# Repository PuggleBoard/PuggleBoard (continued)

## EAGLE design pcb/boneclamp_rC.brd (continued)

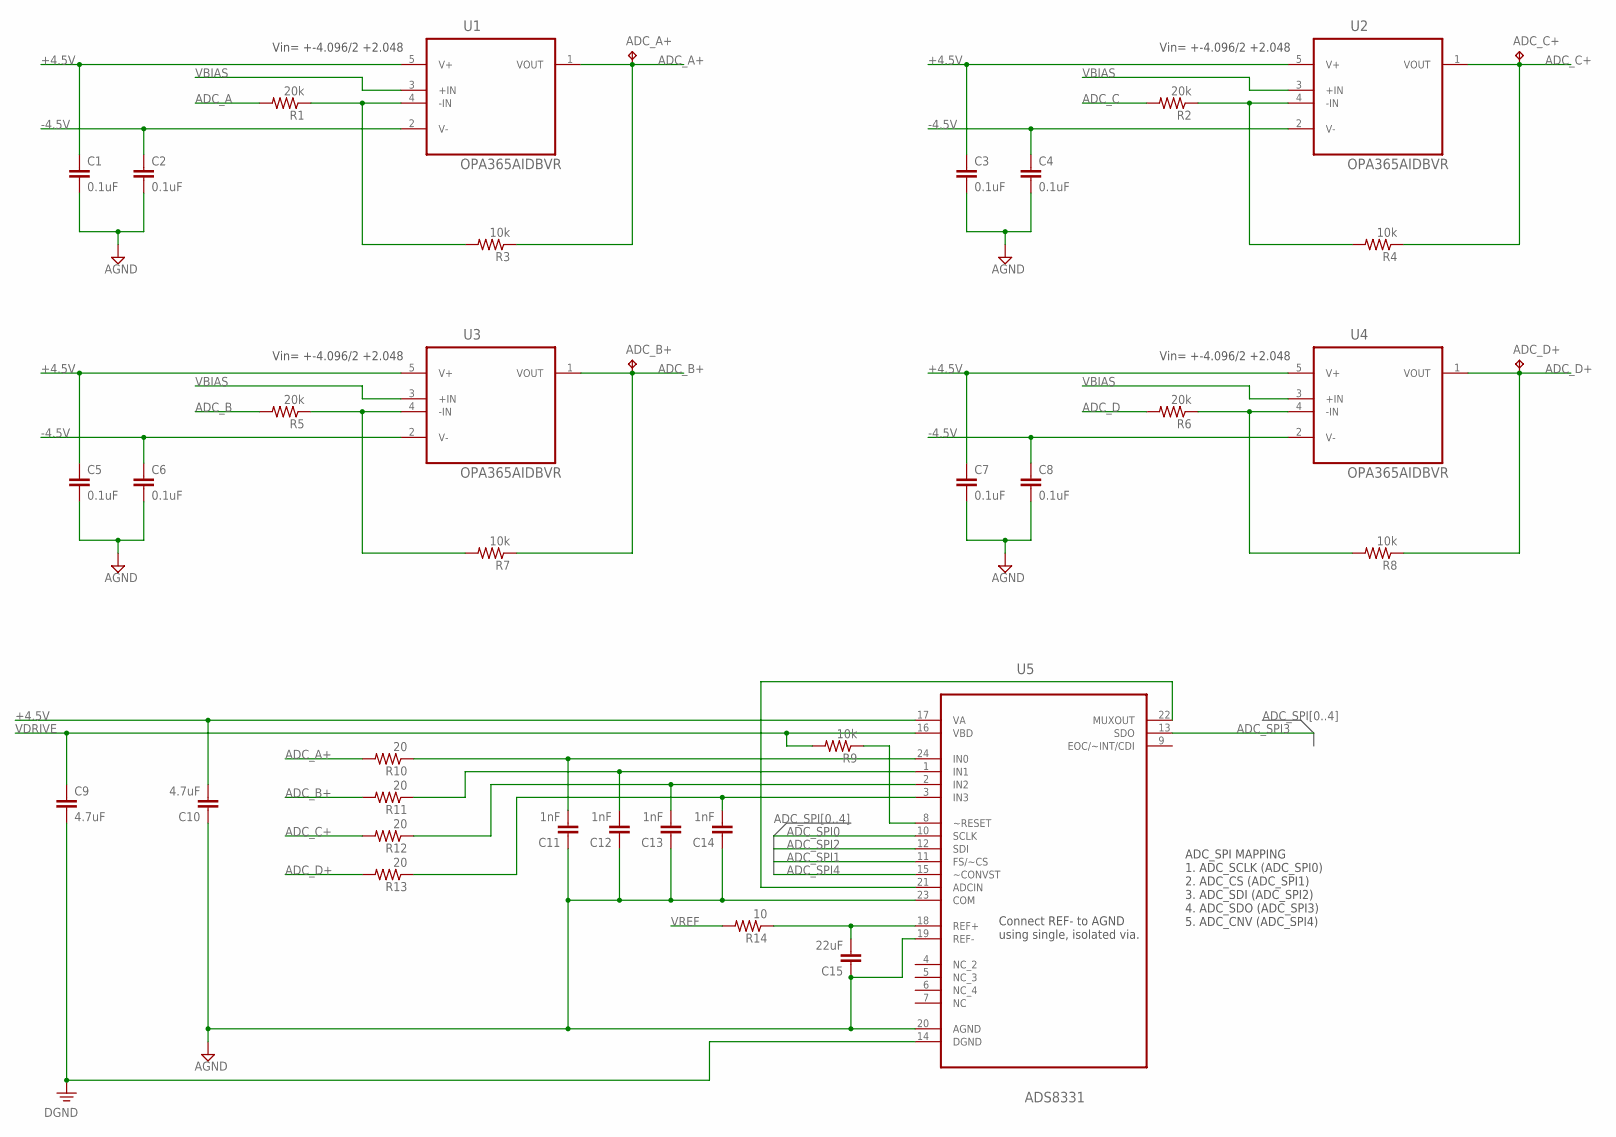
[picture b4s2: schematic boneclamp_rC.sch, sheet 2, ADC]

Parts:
ADC_A+: TPB1,27; B1,27
ADC_B+: TPB1,27; B1,27
ADC_C+: TPB1,27; B1,27
ADC_D+: TPB1,27; B1,27
C1, C2, C3, C4, C5, C6, C7, C8: 0.1uF; C0603
C9, C10: 4.7uF; C0805
C11, C12, C13, C14: 1nF; C0603
C15: 22uF; C0603
R1, R2, R5, R6: 20k; R0603
R3, R4, R7, R8, R9: 10k; R0603
R10, R11, R12, R13: 20; R0603
R14: 10; R0603
U1, U2, U3, U4: OPA365AIDBVR; SOT95P280X145-5N
U5: ADS8331; SOP65P640X120-24N

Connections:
+4.5V: C1.1, C3.1, C5.1, C7.1, C10.2, U1.5 (V+), U2.5 (V+), U3.5 (V+), U4.5 (V+), U5.17 (VA); also elsewhere on the board
-4.5V: C2.1, C4.1, C6.1, C8.1, U1.2 (V-), U2.2 (V-), U3.2 (V-), U4.2 (V-); also elsewhere on the board
ADC_A: R1.2; also elsewhere on the board
ADC_A+: ADC_A+.TP, R3.1, R10.2, U1.1 (VOUT)
ADC_B: R5.2; also elsewhere on the board
ADC_B+: ADC_B+.TP, R7.1, R11.2, U3.1 (VOUT)
ADC_C: R2.2; also elsewhere on the board
ADC_C+: ADC_C+.TP, R4.1, R12.2, U2.1 (VOUT)
ADC_D: R6.2; also elsewhere on the board
ADC_D+: ADC_D+.TP, R8.1, R13.2, U4.1 (VOUT)
ADC_SPI0: U5.10 (SCLK); also elsewhere on the board
ADC_SPI1: U5.11 (FS/~CS); also elsewhere on the board
ADC_SPI2: U5.12 (SDI); also elsewhere on the board
ADC_SPI3: U5.13 (SDO); also elsewhere on the board
ADC_SPI4: U5.15 (~CONVST); also elsewhere on the board
AGND: C1.2, C2.2, C3.2, C4.2, C5.2, C6.2, C7.2, C8.2, C10.1, C11.1, C12.1, C13.1, C14.1, C15.1, U5.19 (REF-), U5.20 (AGND), U5.23 (COM); also elsewhere on the board
DGND: C9.2, U5.14 (DGND); also elsewhere on the board
unnamed: R1.1, R3.2, U1.4 (-IN)
unnamed: R5.1, R7.2, U3.4 (-IN)
unnamed: R2.1, R4.2, U2.4 (-IN)
unnamed: R6.1, R8.2, U4.4 (-IN)
unnamed: C15.2, R14.1, U5.18 (REF+)
unnamed: U5.21 (ADCIN), U5.22 (MUXOUT)
unnamed: C11.2, R10.1, U5.24 (IN0)
unnamed: C12.2, R11.1, U5.1 (IN1)
unnamed: C13.2, R12.1, U5.2 (IN2)
unnamed: C14.2, R13.1, U5.3 (IN3)
VBIAS: U1.3 (+IN), U2.3 (+IN), U3.3 (+IN), U4.3 (+IN); also elsewhere on the board
VDRIVE: C9.1, R9.2, U5.16 (VBD); also elsewhere on the board
VREF: R14.2; also elsewhere on the board
~RST: R9.1, U5.8 (~RESET); also elsewhere on the board

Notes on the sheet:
Connect REF- to AGND using single, isolated via.
Vin= +-4.096/2 +2.048
ADC_SPI MAPPING 1. ADC_SCLK (ADC_SPI0) 2. ADC_CS (ADC_SPI1) 3. ADC_SDI (ADC_SPI2) 4. ADC_SDO (ADC_SPI3) 5. ADC_CNV (ADC_SPI4)

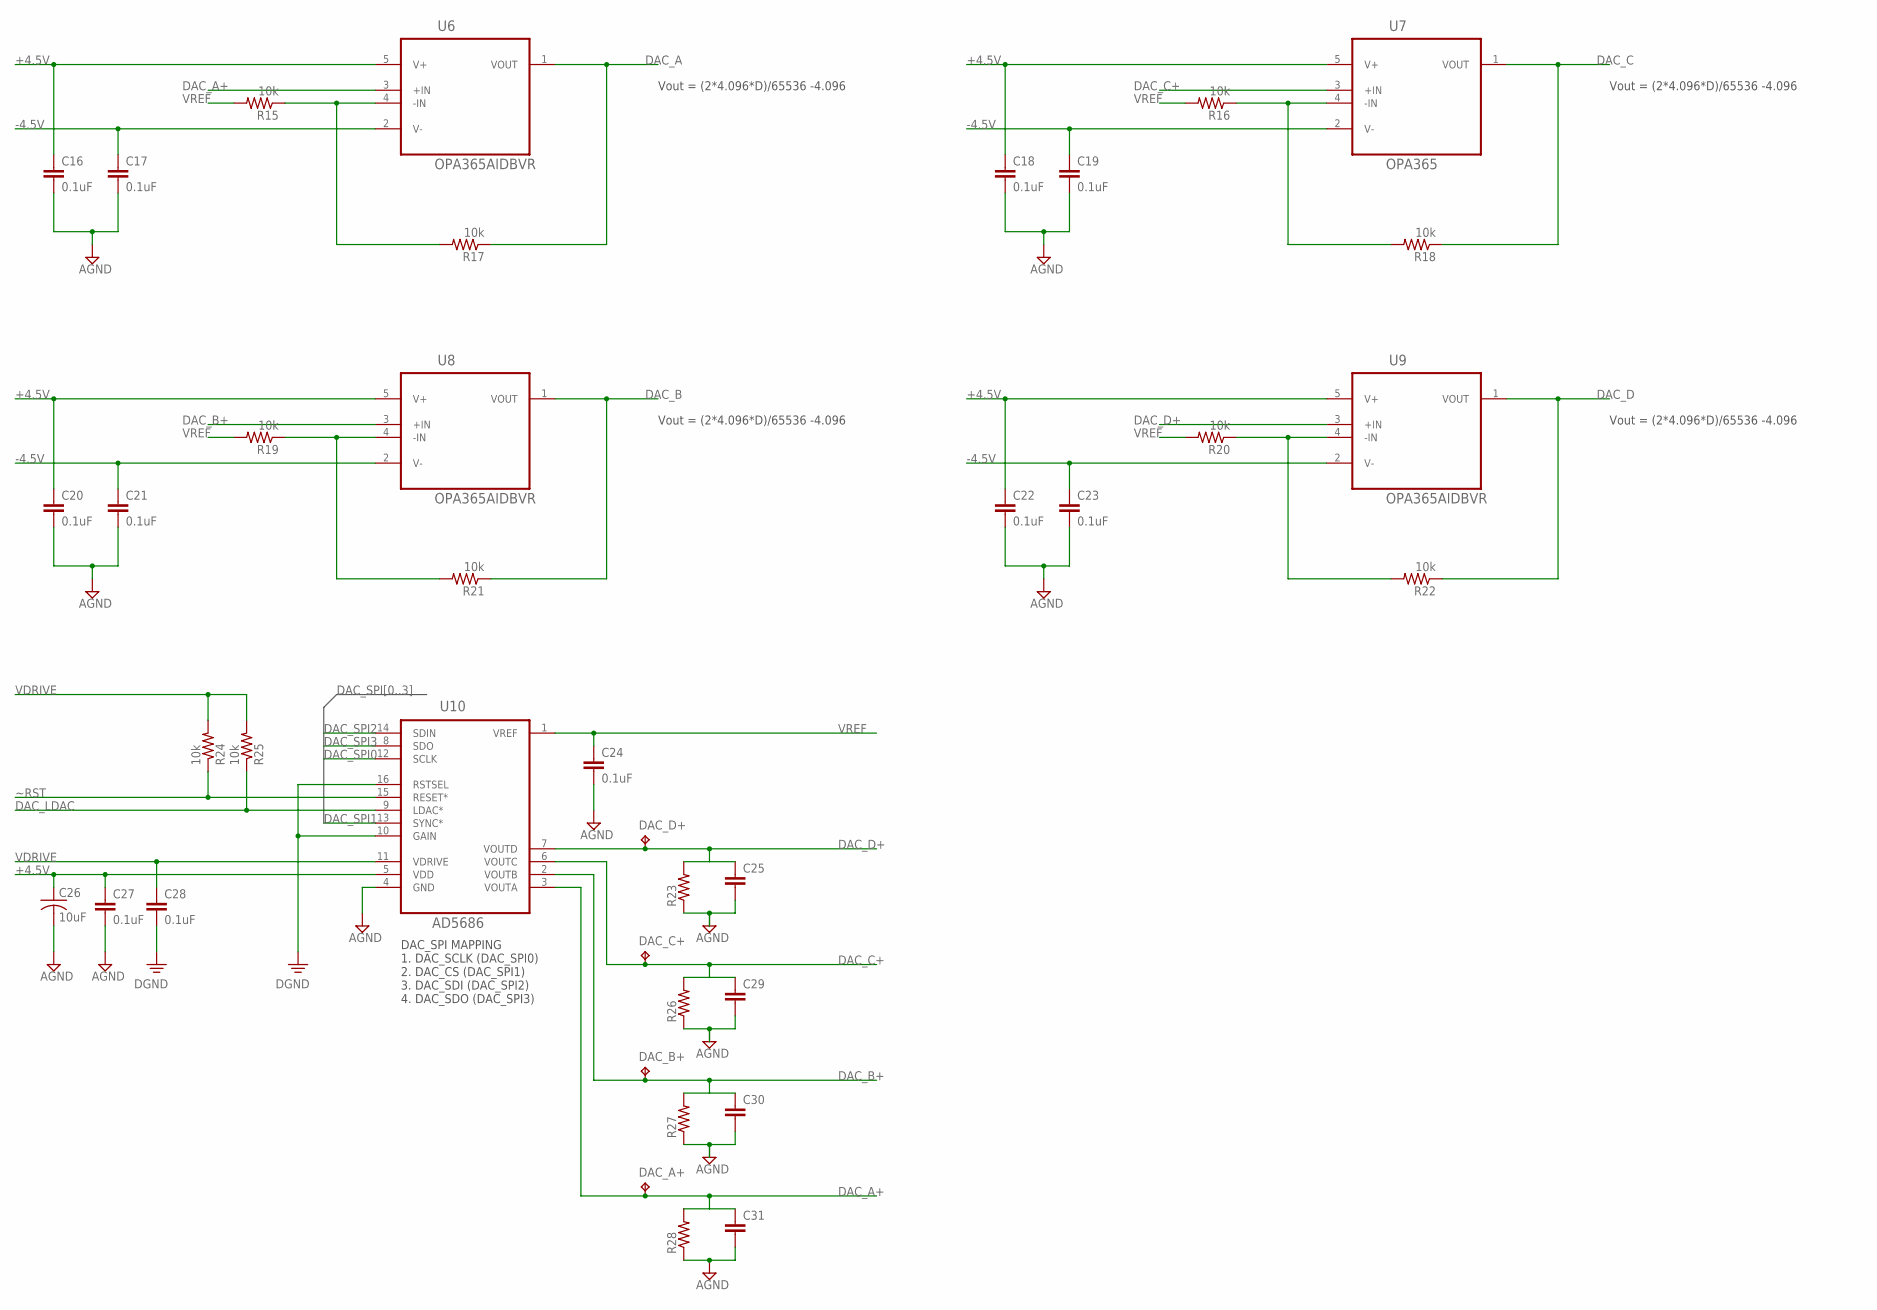
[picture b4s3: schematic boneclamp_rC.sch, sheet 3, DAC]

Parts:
C16, C17, C18, C19, C20, C21, C22, C23, C24, C27, C28: 0.1uF; C0603
C25, C29, C30, C31: C-EUC0603; C0603
C26: 10uF; C0805
DAC_A+: TPB1,27; B1,27
DAC_B+: TPB1,27; B1,27
DAC_C+: TPB1,27; B1,27
DAC_D+: TPB1,27; B1,27
R15, R16, R17, R18, R19, R20, R21, R22, R24, R25: 10k; R0603
R23, R26, R27, R28: R-US_R0603; R0603
U6, U8, U9: OPA365AIDBVR; SOT95P280X145-5N
U7: OPA365; SOT95P280X145-5N
U10: AD5686; MO-153-AB

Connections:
+4.5V: C16.1, C18.1, C20.1, C22.1, C26.1, C27.1, U6.5 (V+), U7.5 (V+), U8.5 (V+), U9.5 (V+), U10.5 (VDD); also elsewhere on the board
-4.5V: C17.1, C19.1, C21.1, C23.1, U6.2 (V-), U7.2 (V-), U8.2 (V-), U9.2 (V-); also elsewhere on the board
AGND: C16.2, C17.2, C18.2, C19.2, C20.2, C21.2, C22.2, C23.2, C24.2, C25.2, C26.2, C27.2, C29.2, C30.2, C31.2, R23.1, R26.1, R27.1, R28.1, U10.4 (GND); also elsewhere on the board
DAC_A: R17.1, U6.1 (VOUT); also elsewhere on the board
DAC_A+: C31.1, DAC_A+.TP, R28.2, U6.3 (+IN), U10.3 (VOUTA)
DAC_B: R21.1, U8.1 (VOUT); also elsewhere on the board
DAC_B+: C30.1, DAC_B+.TP, R27.2, U8.3 (+IN), U10.2 (VOUTB)
DAC_C: R18.1, U7.1 (VOUT); also elsewhere on the board
DAC_C+: C29.1, DAC_C+.TP, R26.2, U7.3 (+IN), U10.6 (VOUTC)
DAC_D: R22.1, U9.1 (VOUT); also elsewhere on the board
DAC_D+: C25.1, DAC_D+.TP, R23.2, U9.3 (+IN), U10.7 (VOUTD)
DAC_LDAC: R25.1, U10.9 (LDAC*)
DAC_SPI0: U10.12 (SCLK); also elsewhere on the board
DAC_SPI1: U10.13 (SYNC*); also elsewhere on the board
DAC_SPI2: U10.14 (SDIN); also elsewhere on the board
DAC_SPI3: U10.8 (SDO); also elsewhere on the board
DGND: C28.2, U10.10 (GAIN), U10.16 (RSTSEL); also elsewhere on the board
unnamed: R16.1, R18.2, U7.4 (-IN)
unnamed: R19.1, R21.2, U8.4 (-IN)
unnamed: R20.1, R22.2, U9.4 (-IN)
unnamed: R15.1, R17.2, U6.4 (-IN)
VDRIVE: C28.1, R24.2, R25.2, U10.11 (VDRIVE); also elsewhere on the board
VREF: C24.1, R15.2, R16.2, R19.2, R20.2, U10.1 (VREF); also elsewhere on the board
~RST: R24.1, U10.15 (RESET*); also elsewhere on the board

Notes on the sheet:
Vout = (2*4.096*D)/65536 -4.096
DAC_SPI MAPPING 1. DAC_SCLK (DAC_SPI0) 2. DAC_CS (DAC_SPI1) 3. DAC_SDI (DAC_SPI2) 4. DAC_SDO (DAC_SPI3)

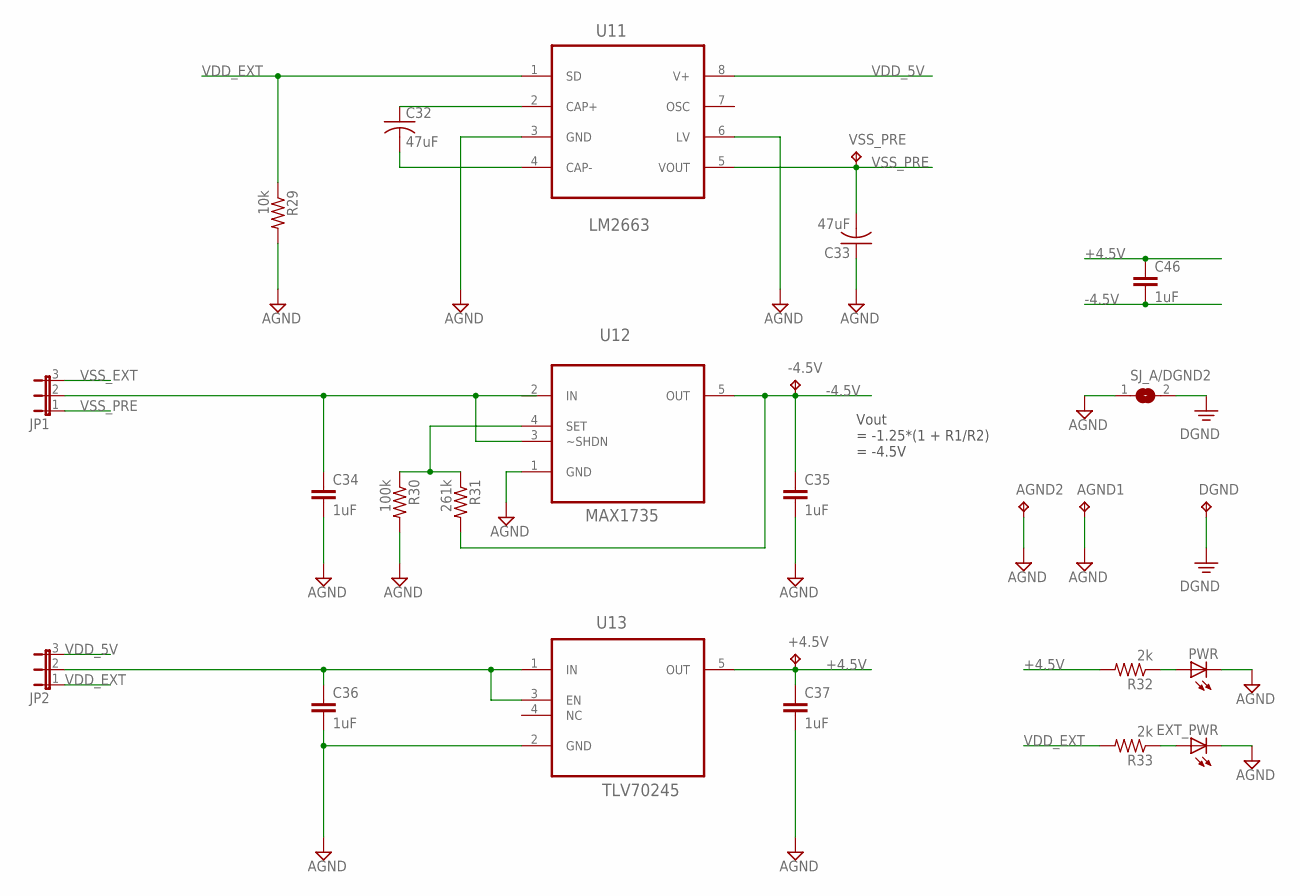
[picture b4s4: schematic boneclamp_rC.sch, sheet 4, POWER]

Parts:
+4.5V: TPPAD1-17; P1-17
-4.5V: TPB1,27; B1,27
AGND1, AGND2: TPPAD1-17; P1-17
C32, C33: 47uF; C1206
C34, C35, C36, C37, C46: 1uF; C0603
DGND: TPPAD1-17; P1-17
EXT_PWR: LEDCHIPLED_0805; CHIPLED_0805
JP1, JP2: JP2E; JP2
PWR: LEDCHIPLED_0805; CHIPLED_0805
R29: 10k; R0603
R30: 100k; R0603
R31: 261k; R0603
R32, R33: 2k; R0603
SJ_A/DGND2: SJ
U11: LM2663; SOIC127P600X175-8N
U12: MAX1735; SOT95P280X145-5N
U13: TLV70245; SOT95P280X110-5N
VSS_PRE: TPB1,27; B1,27

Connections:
+4.5V: +4.5V.TP, C37.1, C46.1, R32.2, U13.5 (OUT); also elsewhere on the board
-4.5V: -4.5V.TP, C35.1, C46.2, R31.2, U12.5 (OUT); also elsewhere on the board
AGND: AGND1.TP, AGND2.TP, C33.1, C34.2, C35.2, C36.2, C37.2, EXT_PWR.C, PWR.C, R29.2, R30.2, SJ_A/DGND2.1, U11.3 (GND), U11.6 (LV), U12.1 (GND), U13.2 (GND); also elsewhere on the board
DGND: DGND.TP, SJ_A/DGND2.2; also elsewhere on the board
unnamed: R30.1, R31.1, U12.4 (SET)
unnamed: EXT_PWR.A, R33.1
unnamed: C36.1, JP2.2, U13.1 (IN), U13.3 (EN)
unnamed: PWR.A, R32.1
unnamed: C34.1, JP1.2, U12.3 (~SHDN)
unnamed: C32.1, U11.2 (CAP+)
unnamed: C32.2, U11.4 (CAP-)
VDD_5V: JP2.3, U11.8 (V+); also elsewhere on the board
VDD_EXT: JP2.1, R29.1, R33.2, U11.1 (SD); also elsewhere on the board
VSS_EXT: JP1.3; also elsewhere on the board
VSS_PRE: C33.2, JP1.1, U11.5 (VOUT), VSS_PRE.TP

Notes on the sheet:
Vout = -1.25*(1 + R1/R2) = -4.5V

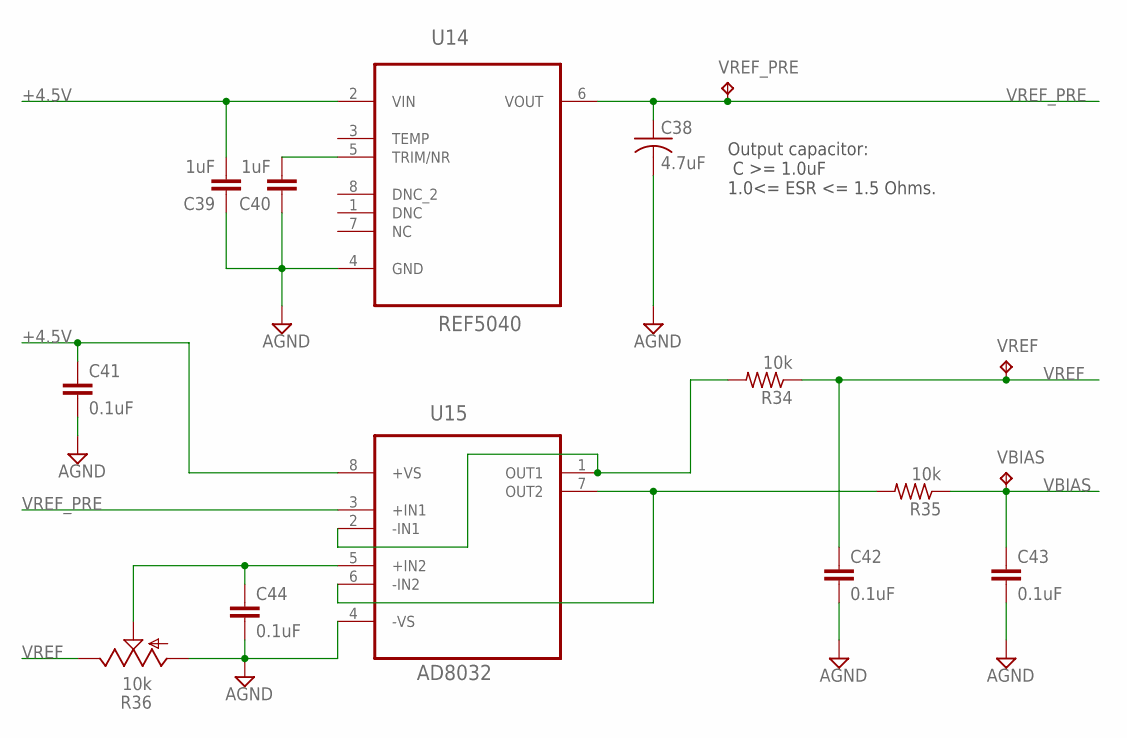
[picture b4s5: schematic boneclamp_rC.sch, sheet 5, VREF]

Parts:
C38: 4.7uF; C1206
C39, C40: 1uF; C0603
C41, C42, C43, C44: 0.1uF; C0603
R34, R35: 10k; R0603
R36: 10k; M84W-TRIMMER
U14: REF5040; SOIC127P600X175-8N
U15: AD8032; SOIC127P600X175-8N
VBIAS: TPB1,27; B1,27
VREF: TPB1,27; B1,27
VREF_PRE: TPB1,27; B1,27

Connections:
+4.5V: C39.2, C41.1, U14.2 (VIN), U15.8 (+VS); also elsewhere on the board
AGND: C38.2, C39.1, C40.1, C41.2, C42.2, C43.2, C44.2, R36.3 (A), U14.4 (GND), U15.4 (-VS); also elsewhere on the board
unnamed: C44.1, R36.2 (S), U15.5 (+IN2)
unnamed: R35.2, U15.6 (-IN2), U15.7 (OUT2)
unnamed: R34.2, U15.1 (OUT1), U15.2 (-IN1)
unnamed: C40.2, U14.5 (TRIM/NR)
VBIAS: C43.1, R35.1, VBIAS.TP; also elsewhere on the board
VREF: C42.1, R34.1, R36.1 (E), VREF.TP; also elsewhere on the board
VREF_PRE: C38.1, U14.6 (VOUT), U15.3 (+IN1), VREF_PRE.TP

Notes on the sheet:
Output capacitor: C >= 1.0uF 1.0<= ESR <= 1.5 Ohms.

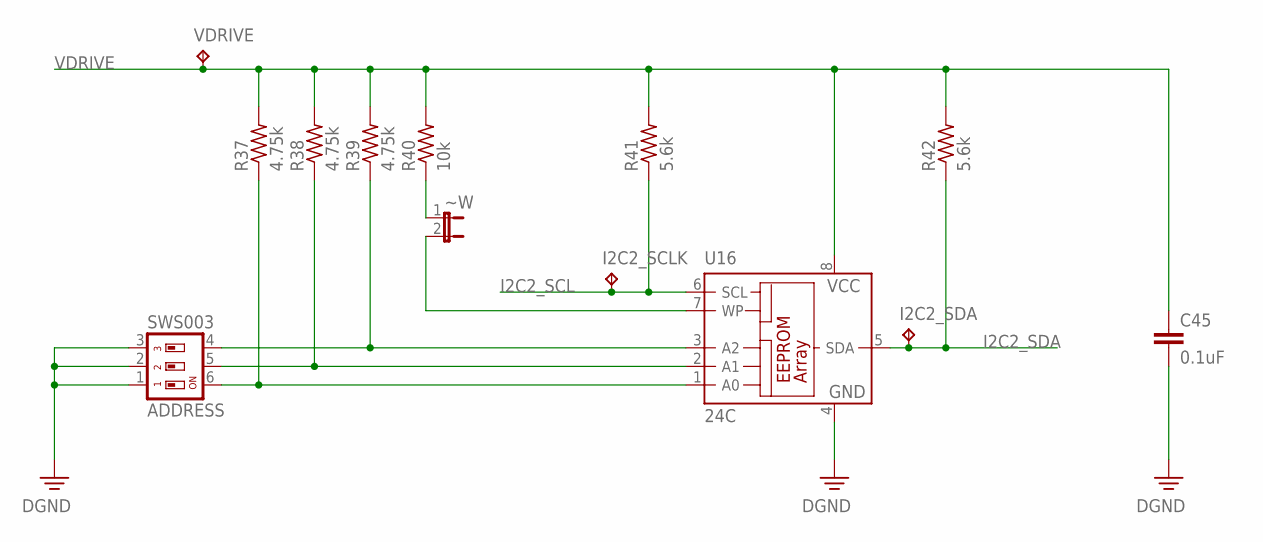
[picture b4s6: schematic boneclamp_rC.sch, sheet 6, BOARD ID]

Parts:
ADDRESS: SWS003; SMS-003
C45: 0.1uF; C0603
I2C2_SCLK, I2C2_SDA: TPB1,27; B1,27
R37, R38, R39: 4.75k; R0603
R40: 10k; R0603
R41, R42: 5.6k; R0603
U16: 24C; SO-08
VDRIVE: TPPAD1-17; P1-17
~W: JP1E; JP1

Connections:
DGND: ADDRESS.1, ADDRESS.2, ADDRESS.3, C45.2, U16.4 (GND); also elsewhere on the board
I2C2_SCL: I2C2_SCLK.TP, R41.1, U16.6 (SCL); also elsewhere on the board
I2C2_SDA: I2C2_SDA.TP, R42.1, U16.5 (SDA); also elsewhere on the board
unnamed: ADDRESS.6, R37.1, U16.1 (A0)
unnamed: ADDRESS.5, R38.1, U16.2 (A1)
unnamed: ADDRESS.4, R39.1, U16.3 (A2)
unnamed: U16.7 (WP), ~W.2
unnamed: R40.1, ~W.1
VDRIVE: C45.1, R37.2, R38.2, R39.2, R40.2, R41.2, R42.2, U16.8 (VCC), VDRIVE.TP; also elsewhere on the board

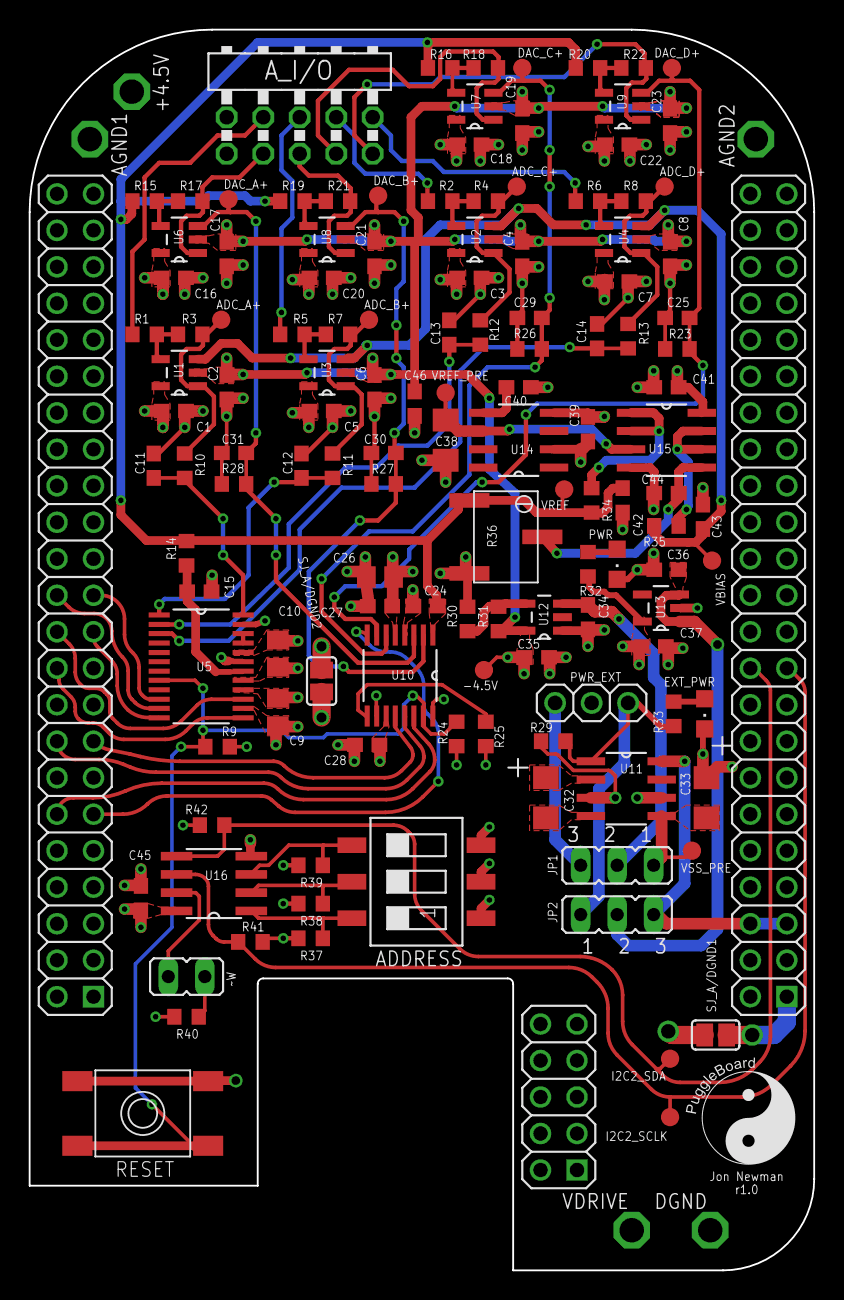
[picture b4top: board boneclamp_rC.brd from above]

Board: 4 copper layers, 54.6 x 86.4 mm, 136 parts (0 on the bottom side), 73 nets.

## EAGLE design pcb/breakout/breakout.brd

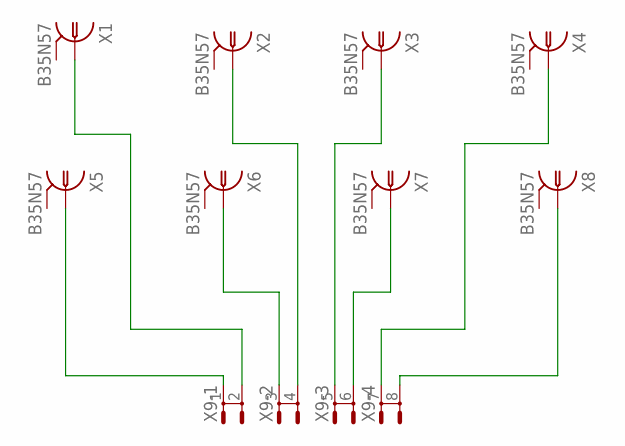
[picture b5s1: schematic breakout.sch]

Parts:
X1, X2, X3, X4, X5, X6, X7, X8: B35N57
X9: SH5-4

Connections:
unnamed: X5.1, X9.1
unnamed: X1.1, X9.2
unnamed: X6.1, X9.3 (1)
unnamed: X2.1, X9.4 (2)
unnamed: X3.1, X9.5 (1)
unnamed: X7.1, X9.6 (2)
unnamed: X4.1, X9.7 (1)
unnamed: X8.1, X9.8 (2)

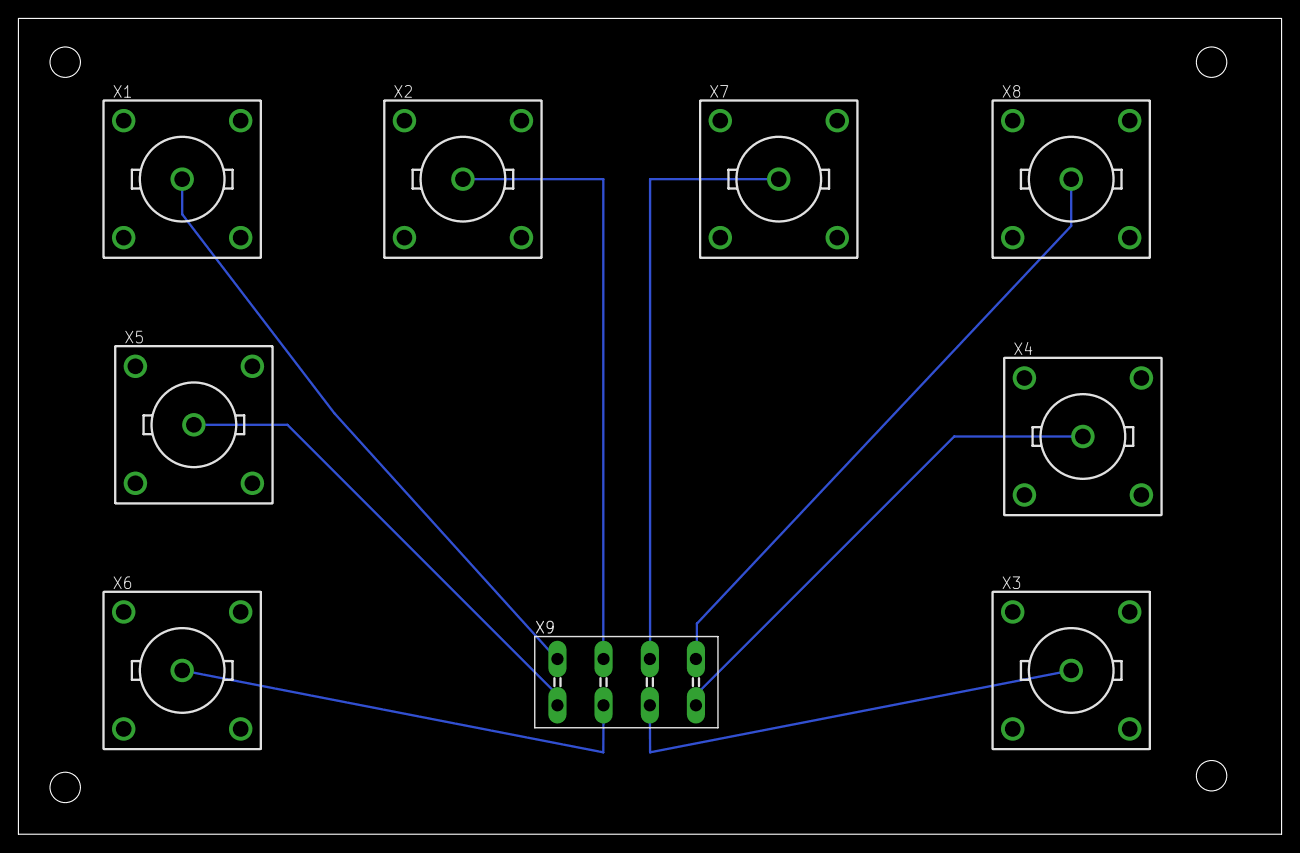
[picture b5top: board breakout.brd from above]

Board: 2 copper layers, 137.1 x 88.6 mm, 9 parts (0 on the bottom side), 8 nets.
